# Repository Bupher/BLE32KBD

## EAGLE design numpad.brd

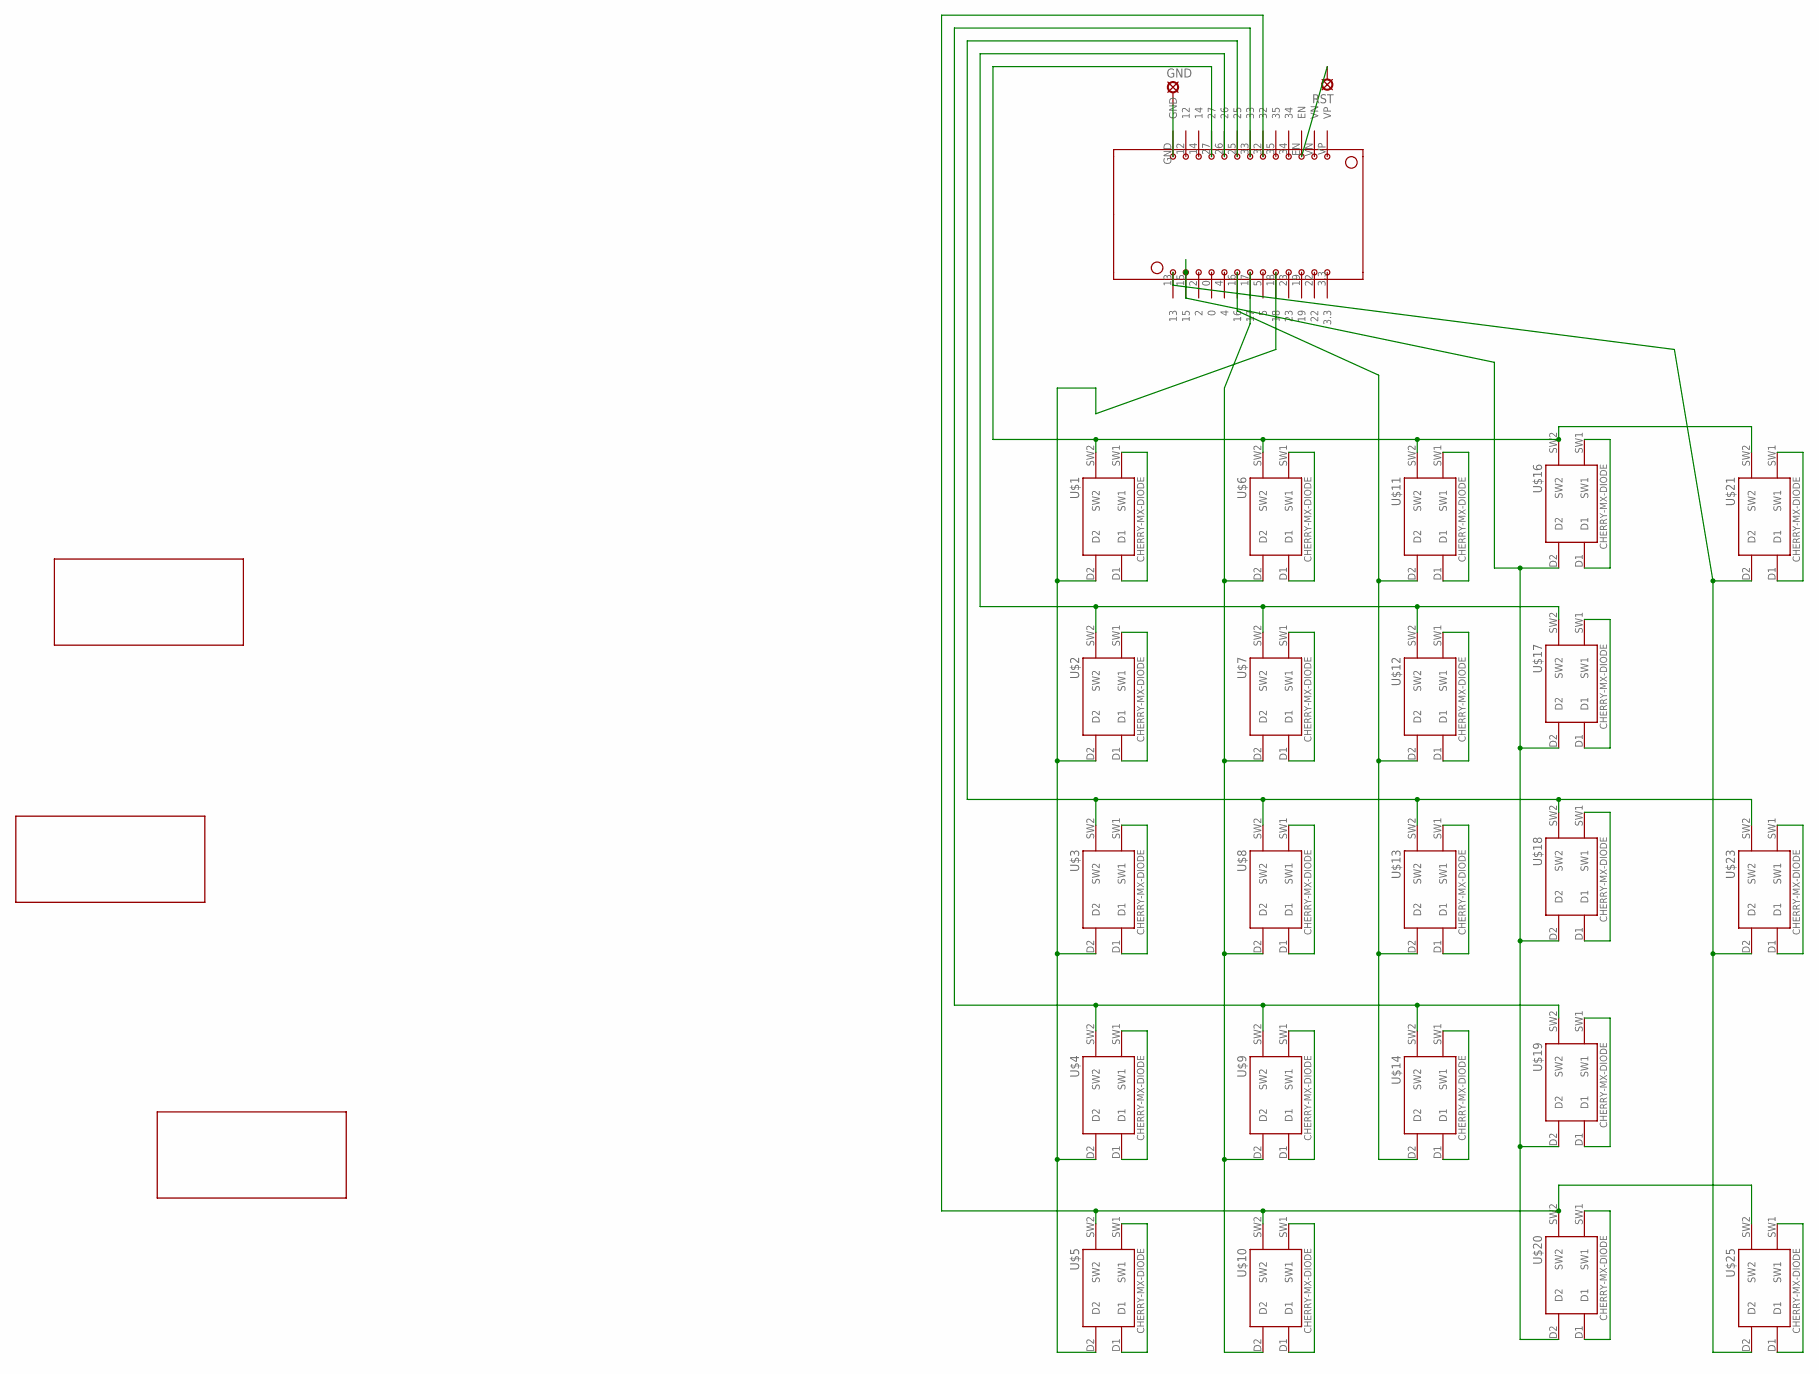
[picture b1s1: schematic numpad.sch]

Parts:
GND: LSP10
RST: LSP10
U$1, U$2, U$3, U$4, U$5, U$6, U$7, U$8, U$9, U$10, U$11, U$12, U$13, U$14, U$16, U$17, U$18, U$19, U$20, U$21, U$23, U$25: CHERRY-MX-DIODE
U$15, U$22, U$24: 2U
U$27: ESP32OFFBRAND

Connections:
unnamed: U$1.D1, U$1.SW1
unnamed: U$2.D1, U$2.SW1
unnamed: U$3.D1, U$3.SW1
unnamed: U$4.D1, U$4.SW1
unnamed: U$5.D1, U$5.SW1
unnamed: U$6.D1, U$6.SW1
unnamed: U$7.D1, U$7.SW1
unnamed: U$8.D1, U$8.SW1
unnamed: U$9.D1, U$9.SW1
unnamed: U$10.D1, U$10.SW1
unnamed: U$6.D2, U$7.D2, U$8.D2, U$9.D2, U$10.D2, U$27.17
unnamed: U$11.D1, U$11.SW1
unnamed: U$12.D1, U$12.SW1
unnamed: U$13.D1, U$13.SW1
unnamed: U$14.D1, U$14.SW1
unnamed: U$11.D2, U$12.D2, U$13.D2, U$14.D2, U$27.16
unnamed: U$16.D1, U$16.SW1
unnamed: U$17.D1, U$17.SW1
unnamed: U$18.D1, U$18.SW1
unnamed: U$19.D1, U$19.SW1
unnamed: U$20.D1, U$20.SW1
unnamed: U$16.D2, U$17.D2, U$18.D2, U$19.D2, U$20.D2, U$27.15
unnamed: U$21.D1, U$21.SW1
unnamed: U$23.D1, U$23.SW1
unnamed: U$25.D1, U$25.SW1
unnamed: U$21.D2, U$23.D2, U$25.D2, U$27.13
unnamed: U$1.SW2, U$6.SW2, U$11.SW2, U$16.SW2, U$21.SW2, U$27.27
unnamed: U$2.SW2, U$7.SW2, U$12.SW2, U$17.SW2, U$27.26
unnamed: U$3.SW2, U$8.SW2, U$13.SW2, U$18.SW2, U$23.SW2, U$27.25
unnamed: U$4.SW2, U$9.SW2, U$14.SW2, U$19.SW2, U$27.33
unnamed: U$5.SW2, U$10.SW2, U$20.SW2, U$25.SW2, U$27.32
unnamed: U$1.D2, U$2.D2, U$3.D2, U$4.D2, U$5.D2, U$27.18
unnamed: GND.MP, U$27.GND
unnamed: RST.MP, U$27.EN

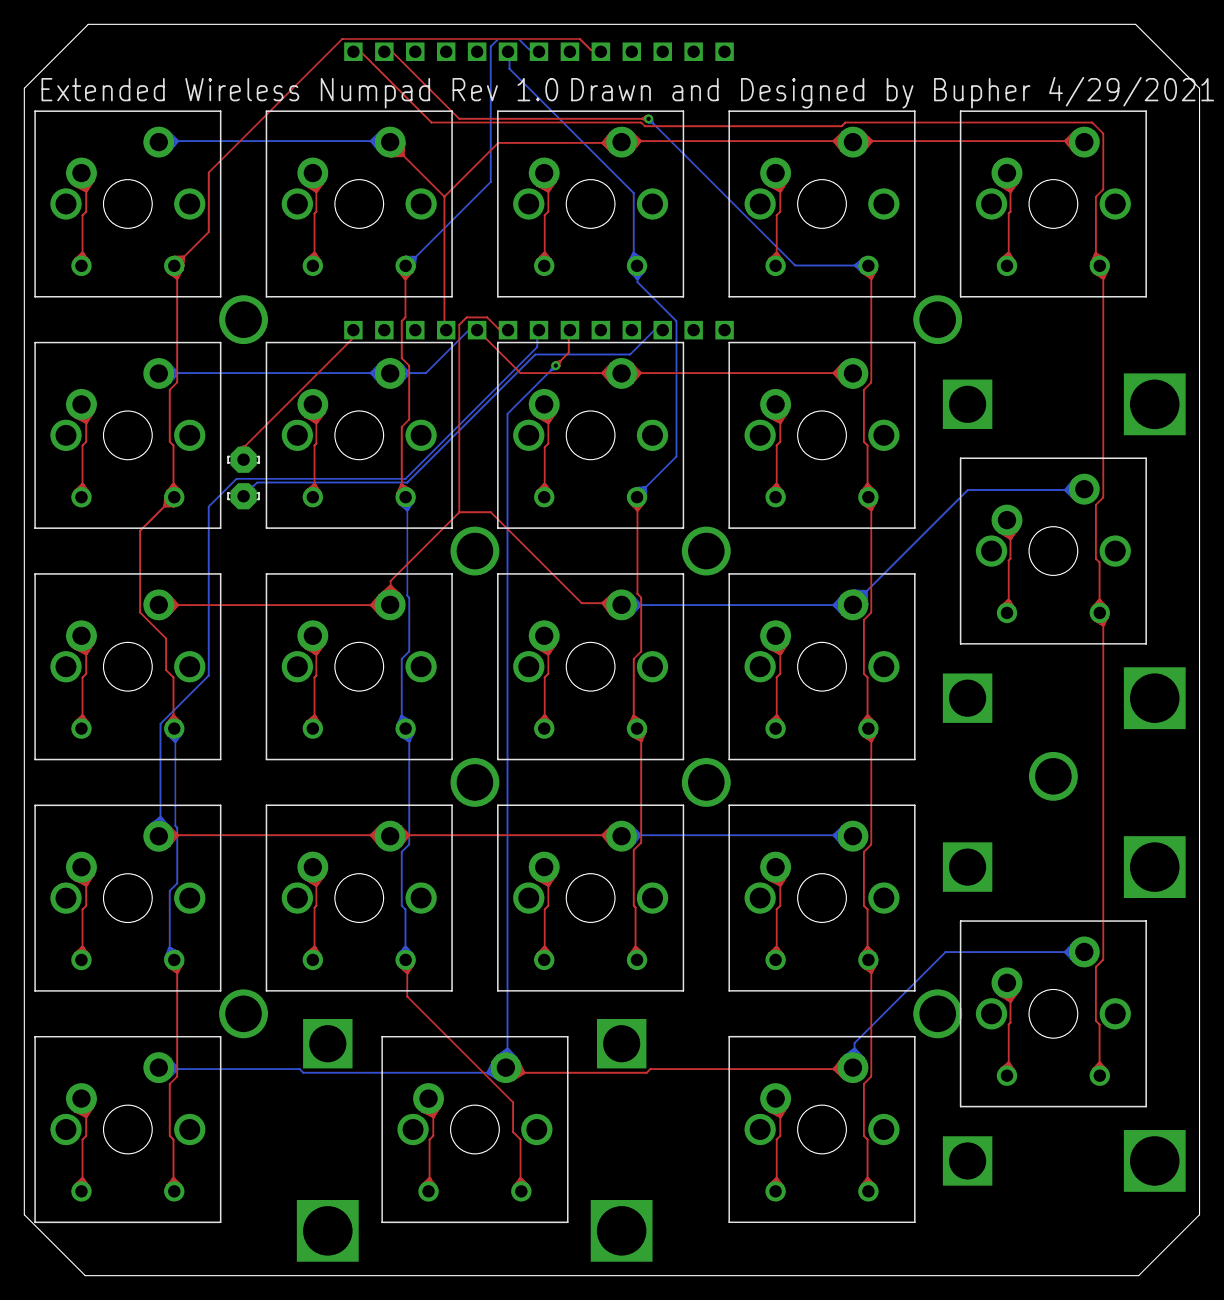
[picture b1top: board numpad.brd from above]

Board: 2 copper layers, 96.5 x 102.8 mm, 28 parts (1 on the bottom side), 34 nets.

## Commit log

2021-09-15 Eagle Files
